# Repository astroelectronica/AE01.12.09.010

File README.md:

# AE01.12.09.010
MAX713
NiCd/NiMH battery fast-charge controller

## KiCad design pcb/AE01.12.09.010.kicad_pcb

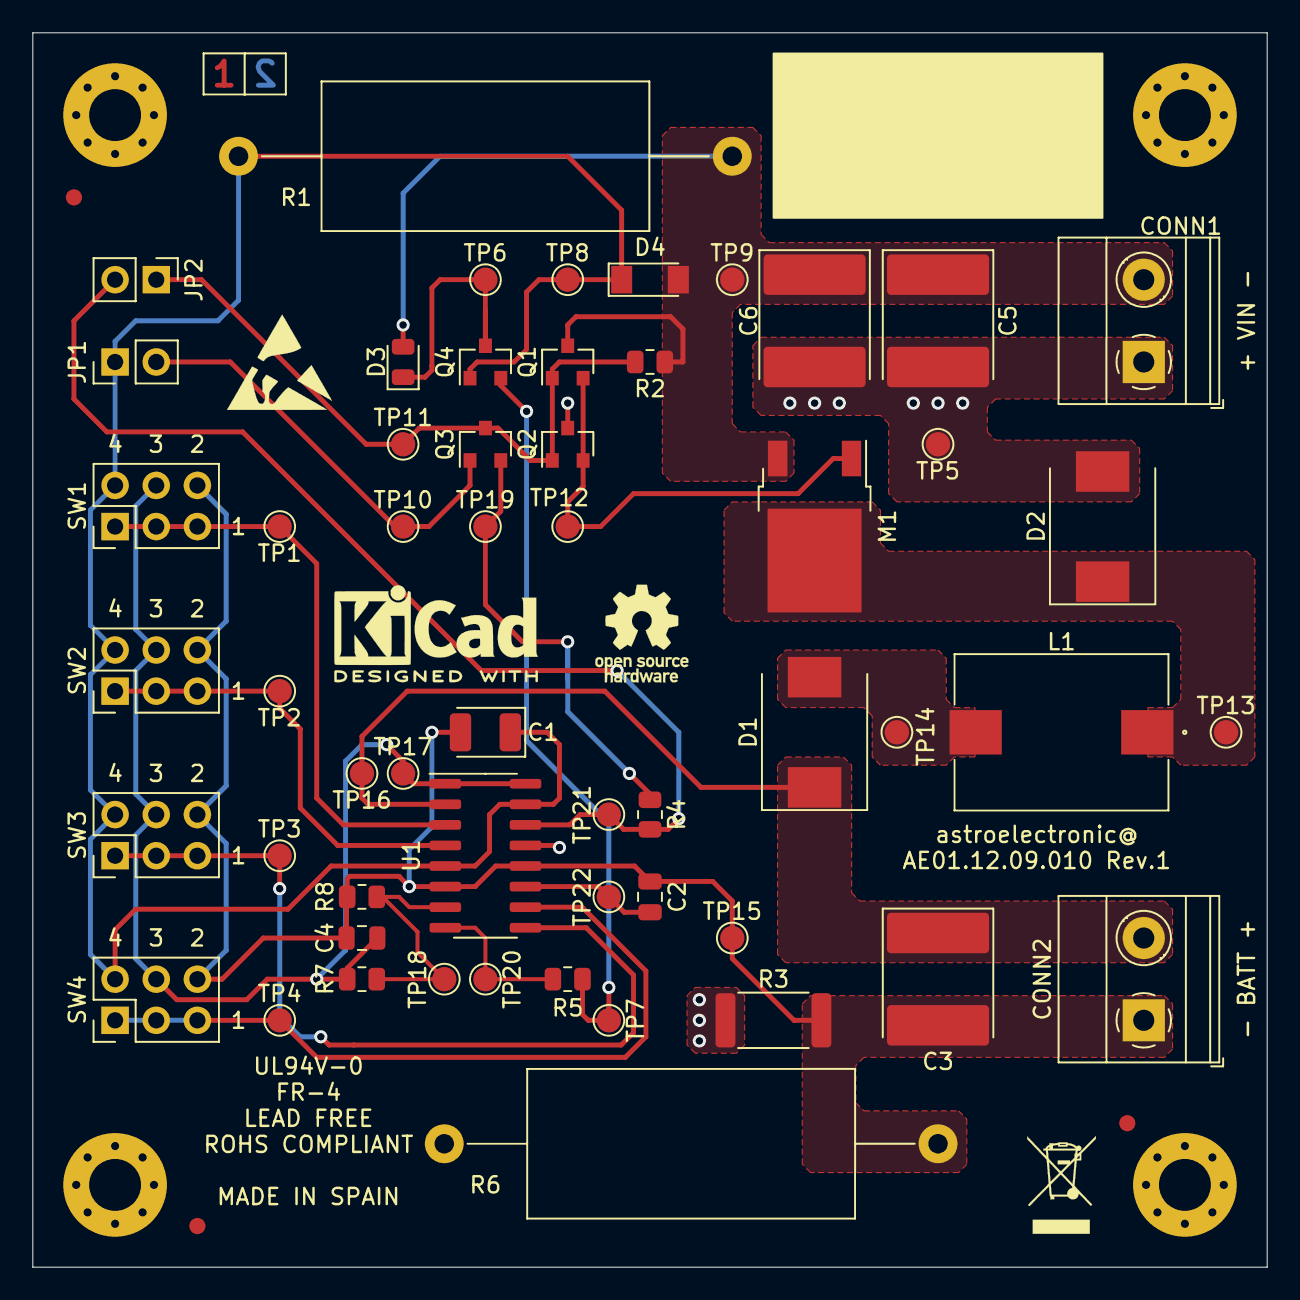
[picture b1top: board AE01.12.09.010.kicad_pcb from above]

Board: 2 copper layers, 76.2 x 76.2 mm, 66 parts (0 on the bottom side), 22 nets.

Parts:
C1: 1uF/10V; CP_EIA-3528-21_Kemet-B
C2: 220pF; C_0805_2012Metric
C3, C5, C6: 10uF/50V; CP_EIA-7260-38_AVX-R
C4: 100nF; C_0805_2012Metric
CONN1: VIN; TerminalBlock_Phoenix_MKDS-1,5-2-5.08_1x02_P5.08mm_Horizont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
CONN2: BATT; TerminalBlock_Phoenix_MKDS-1,5-2-5.08_1x02_P5.08mm_Horizont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
D1, D2: MBRS340T3; D_SMC
D3: LED_ALT; LED_0805_2012Metric
D4: CCLHM080; D_MiniMELF
FID1, FID2, FID3: Fiducial; Fiducial_1mm_Mask2mm
H1, H2, H3, H4: M3; MountingHole_3.2mm_M3_Pad_Via
JP1, JP2: Jumper; PinHeader_1x02_P2.54mm_Vertical
L1: DO3340; DO3340P-223MLB
LOGO1: SYM_ESD_Small; ESD-Logo_6.6x6mm_SilkScreen
LOGO2: Logo_Open_Hardware_Small; OSHW-Logo_5.7x6mm_SilkScreen
LOGO3: WEEE; WEEE-Logo_4.2x6mm_SilkScreen
LOGO4: KICAD; KiCad-Logo2_5mm_SilkScreen
M1: IRFR9024; TO-252-2
Q1, Q3, Q4: CMPTA06; SOT-23
Q2: MMBT2907ALT1; SOT-23
R1, R6: DNP; R_Axial_DIN0922_L20.0mm_D9.0mm_P30.48mm_Horizontal
R2: 5.1K; R_0805_2012Metric
R3: 0.25R; R_2512_6332Metric
R4: 1.5K; R_0805_2012Metric
R5: 470R; R_0805_2012Metric
R7: 68K; R_0805_2012Metric
R8: 22K; R_0805_2012Metric
SW1: SW1; PinHeader_2x03_P2.54mm_Vertical
SW2: SW2; PinHeader_2x03_P2.54mm_Vertical
SW3: SW3; PinHeader_2x03_P2.54mm_Vertical
SW4: SW4; PinHeader_2x03_P2.54mm_Vertical
TP1, TP2, TP3, TP4, TP5, TP6, TP7, TP8, TP9, TP10, TP11, TP12, TP13, TP14, TP15, TP16, TP17, TP18, TP19, TP20, TP21, TP22: TestPoint; TestPoint_Pad_D1.5mm
U1: MAX713CSE; SOIC-16_3.9x9.9mm_P1.27mm

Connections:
/BATT+: C3.1, CONN2.2, D1.1, TP16.1, U1.2
/BATT-: C1.2, C2.1, C3.2, C4.2, CONN2.1, R3.1, R6.1, R8.2, SW1.6, SW2.6, SW3.6, SW4.6, TP15.1, U1.6, U1.12
/CC: C2.2, TP22.1, U1.11
/DRV: JP2.2, R4.2, TP21.1, U1.14
/LED: D3.1, Q4.3, TP6.1
/PGM0: SW1.1, SW1.3, SW1.5, TP1.1, U1.3
/PGM1: SW2.1, SW2.3, SW2.5, TP2.1, U1.4
/PGM2: SW3.1, SW3.3, SW3.5, TP3.1, U1.9
/PGM3: SW4.1, SW4.3, SW4.5, TP4.1, U1.10
/REF: C4.1, R7.1, SW1.4, SW2.4, SW3.4, SW4.4, TP17.1, U1.1, U1.16
/TEMP: R7.2, R8.1, TP18.1, U1.7
/V+: C1.1, D4.1, JP1.1, Q4.1, R1.2, SW1.2, SW2.2, SW3.2, SW4.2, TP8.1, U1.5, U1.15
/VIN: C5.1, C6.1, CONN1.2, D3.2, D4.2, M1.3, Q1.3, R1.1, R2.1, TP9.1
/~FASTCHG: R5.1, TP20.1, U1.8
GND: C5.2, C6.2, CONN1.1, D2.2, Q2.3, R3.2, R6.2, TP5.1, U1.13
unnamed: D1.2, L1.2, TP14.1
unnamed: D2.1, L1.1, M1.2, TP13.1
unnamed: JP1.2, Q3.1, TP10.1
unnamed: JP2.1, Q1.1, Q2.1, Q3.3, R2.2, TP11.1
unnamed: M1.1, Q1.2, Q2.2, TP12.1
unnamed: Q3.2, R4.1, TP19.1
unnamed: Q4.2, R5.2, TP7.1

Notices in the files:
parts and their libraries:
Copyright 2021 Accelerated Designs. All rights reserved.
